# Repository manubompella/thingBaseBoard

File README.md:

# thingBaseBoard

The thingBaseBoard hosts the power supply unit, relays, triacs and the connectors for connecting to the thingTouch and the thingBots in a regular 8 module electrical box

## Platform Features

  * [XBee Compatible Socket](https://www.sparkfun.com/datasheets/Wireless/Zigbee/XBee-Dimensional.pdf)
  * Power ON Led
  * 230V Vin
  
## Maintainers

The thingBaseBoard is maintained by thingTronics Innovations.

Main contributor:
 * Manohar Bompella @<manohar.bompella@thingtronics.com>
 * Lovelesh Patel @<lovelesh.patel@thingtronics.com>

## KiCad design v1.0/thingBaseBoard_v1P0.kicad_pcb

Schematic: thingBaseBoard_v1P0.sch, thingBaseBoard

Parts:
C1: 10uF; C_0805_HandSoldering
D1: CONN_LED; LED_0805
D2: TOUCH_LED; LED_0805
D3, D4, D5, D6, D7, D9, D10: 1N4007; D_0805
D8: POWER_LED; LED_0805
F1: FUSE; 8mm_Pitch
P1: AC_230V; gmkds_3-3-5,08
P2: TOUCH_PANEL_CONNECTOR; IDC_Header_Straight_16pins
P3: APPLIANCES_CONNECTOR; gmkds_3-8-5,08
Q1, Q2, Q3, Q4, Q5, Q6: 2N3904-MMBT; TSOT-23
Q7: 2N7002
R1, R2, R9, R11, R13, R15, R19, R22: 100E; R_0805_HandSoldering
R3, R4: 150K; R_Axial_DIN0309_L9.0mm_D3.2mm_P12.70mm_Horizontal
R5, R6, R8, R10, R12, R14, R16, R20, R23, R26, R27, R28, R29: 0E; R_0805_HandSoldering
R7: 10K; R_0805_HandSoldering
R17, R18: 3K3; R_0805_HandSoldering
R21: 470E; R_0805_HandSoldering
R24: 22K; R_0805_HandSoldering
R25: 150K; R_0805_HandSoldering
RL1, RL2, RL3, RL4, RL5, RL6: G5Q-1; Relay_SPDT_OMRON-G5Q
SP1: BUZZER; Buzzer_12x9.5RM7.6
U1: HenLv-AC220S3_3DCS-3W; AC220S3.3DCS-3W HenLv
U2: DF08S1_BRIDGE_REC-IC; DF08S1_DIODE_BRIDGE
U3: XBEE_MODULE; XBee_Socket_without_Jtag
U4, U6: TRIAC_BOARD; Triac_board_v1.0
U5: 4N35_OPTO; 4N35_OPTOCOUPLER
W1: EARTH; SolderWirePad_single_1-2mmDrill

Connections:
+3V3: C1.1, D3.1 (K), D4.1 (K), D5.1 (K), D6.1 (K), D7.1 (K), D9.1 (K), D10.1 (K), P2.1, R1.1, R7.1, R17.1, R18.1, R21.1, RL1.2, RL2.2, RL3.2, RL4.2, RL5.2, RL6.2, SP1.1, U1.4 (3V3), U3.1 (VCC)
BUZZER: P2.9, Q7.1, R24.2
CONNECT_LED: D1.1 (K), R26.2, R28.1
GND: C1.2, D2.1 (K), D8.1 (K), P2.2, Q1.3 (E), Q2.3 (E), Q3.3 (E), Q4.3 (E), Q5.3 (E), Q6.3 (E), Q7.2, R24.1, U1.3 (GND), U3.10 (GND), U4.1 (GND), U5.4 (EMITTER), U6.1 (GND)
I2C_SCL: P2.5, R18.2, U3.19 (AD1/DIO1)
I2C_SDA: P2.3, R17.2, U3.20 (AD0/DIO0)
L: F1.2, R3.2, RL1.3, RL2.3, RL3.3, RL4.3, RL5.3, RL6.3, U1.1 (L), U4.3 (L2), U6.3 (L2)
LS_INTR: P2.15, U3.15 (AD5/DIO5)
N: P1.2, R4.2, U1.2 (N)
unnamed: D1.2 (A), R1.2
unnamed: D2.2 (A), R2.2
unnamed: D3.2 (A), Q1.1 (C), RL1.1
unnamed: D4.2 (A), Q2.1 (C), RL2.1
unnamed: D5.2 (A), Q3.1 (C), RL3.1
unnamed: D6.2 (A), Q4.1 (C), RL4.1
unnamed: D7.2 (A), Q5.1 (C), RL5.1
unnamed: D8.2 (A), R21.2
unnamed: D9.2 (A), Q6.1 (C), RL6.1
unnamed: D10.2 (A), R25.2, SP1.2
unnamed: F1.1, P1.1
unnamed 20: P1.3, W1.1; also elsewhere on the board
unnamed: P3.1, U4.4 (L1)
unnamed: P3.2, U6.4 (L1)
unnamed: P3.3, RL1.5
unnamed: P3.4, RL2.5
unnamed: P3.5, RL3.5
unnamed: P3.6, RL4.5
unnamed: P3.7, RL5.5
unnamed: P3.8, RL6.5
unnamed: Q1.2 (B), R9.1
unnamed: Q2.2 (B), R11.1
unnamed: Q3.2 (B), R13.1
unnamed: Q4.2 (B), R15.1
unnamed: Q5.2 (B), R19.1
unnamed: Q6.2 (B), R22.1
unnamed: Q7.3, R25.1
unnamed: R3.1, U2.4 (AC)
unnamed: R4.1, U2.3 (AC)
unnamed: R5.1, U4.2 (I/P)
unnamed: R6.1, U6.2 (I/P)
unnamed: R7.2, R8.2, U5.5 (COLLECTOR)
unnamed: R9.2, R10.1
unnamed: R11.2, R12.1
unnamed: R13.2, R14.1
unnamed: R15.2, R16.1
unnamed: R19.2, R20.1
unnamed: R22.2, R23.1
unnamed: R26.1, U3.4 (DO8)
unnamed: R27.1, U3.7 (PWM1)
unnamed: R28.2, U3.13 (ON/SLEEP)
unnamed: R29.2, U3.12 (CTS/DIO7)
unnamed: U2.1 (+), U5.1 (ANODE)
unnamed: U2.2 (-), U5.2 (CATHODE)
RELAY_1: P2.14, R10.2
RELAY_2: P2.12, R12.2
RELAY_3: P2.10, R14.2
RELAY_4: P2.8, R16.2
RELAY_5: P2.6, R8.1, R20.2
RELAY_6: P2.4, R23.2
TOUCH_INTR: P2.7, U3.11 (AD4/DIO4)
TOUCH_LED: R2.1, R27.2, R29.1
TRIAC_1: P2.11, R5.2
TRIAC_2: P2.13, R6.2
TS_INTR: P2.16, U3.16 (RTS/AD6/DIO6)

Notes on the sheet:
3V3
I2C_SDA
I2C_SCL
I2C_INTR
BUZZER
TRIAC1
TRIAC2
RELAY_6
RELAY_5
RELAY_4
RELAY_3
RELAY_2
RELAY_1
TS_INTR
LS_INTR
GND
AD0
AD1
AD2
PWM1
PWM3
INTR
PWM0
AD3
V_OUT
SPI_MOSI
SPI_MISO
SPI_nCS
SPI_CLK
nRESET
PWM2
Peripheral Section
Power Supply Section
TOUCH_PANEL_CONNECTOR
XBEE_SOCKET
Appliances Connector
0.5W TH
Zero Cross Signal out
2X8 2.54mm TH Place on Top
2X10 2.0mm TH Female Place on Top

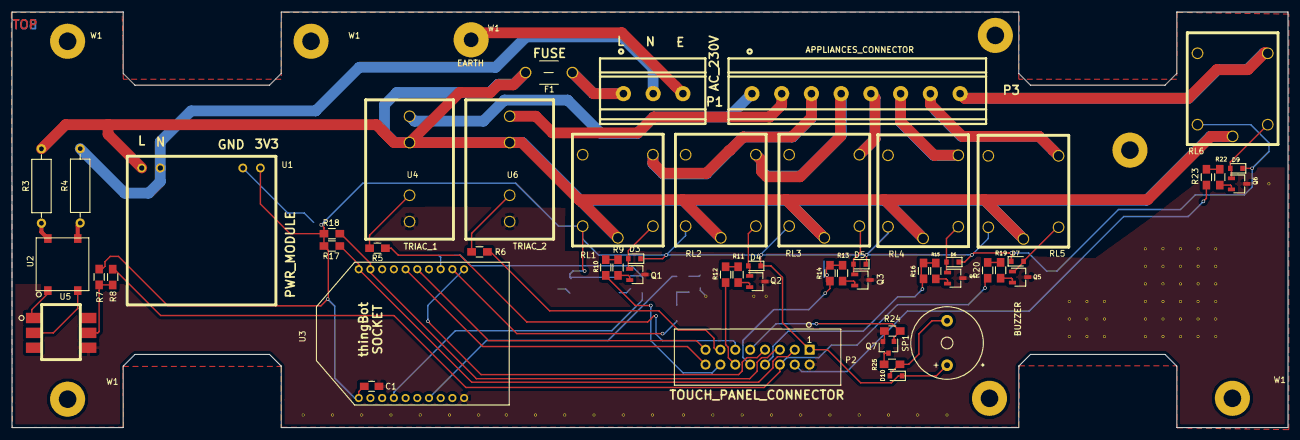
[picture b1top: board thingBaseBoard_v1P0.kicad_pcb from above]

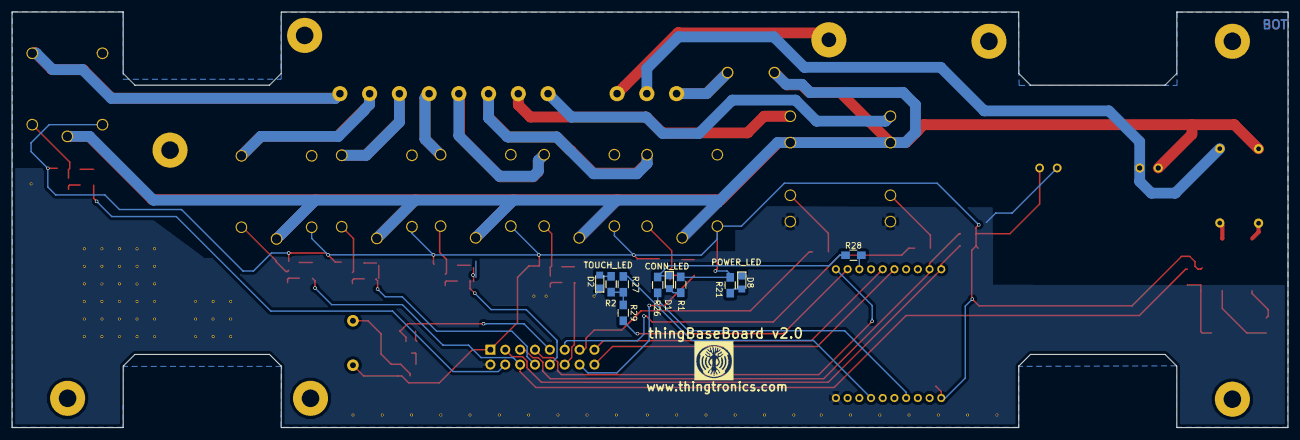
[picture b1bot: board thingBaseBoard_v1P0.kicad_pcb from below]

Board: 2 copper layers, 218.0 x 71.0 mm, 72 parts (10 on the bottom side), 64 nets.

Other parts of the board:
W1#2, W1#3, W1#4, W1#5, W1#6, W1#7, W1#8: EARTH; SolderWirePad_single_2-5mmDrill

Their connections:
unnamed 20: W1#8.1; also elsewhere on the board

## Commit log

2017-02-02 Added directory structure and reference schematic
2017-02-02 Updated README and added 3.3V power supply reference
2017-02-03 Schematic Added
    Schematic Added
    Reference Files Added
2017-02-13 All footprints are placed in Layout
    All footprints are placed in Layout
    - silk Screen Added for all
    - size of the Pcb decreased by 2mm
2017-02-15 Routing done
    routing Completed,
    Power Module footprint Changed,
    2mm size of the PCB reduced.
2017-02-17 Bom Create, Holes made in Layout, Schematic Changed
    - Bom generated
    - in schematic Mosfet Q7 Changed
    - in layout mounting holes made
